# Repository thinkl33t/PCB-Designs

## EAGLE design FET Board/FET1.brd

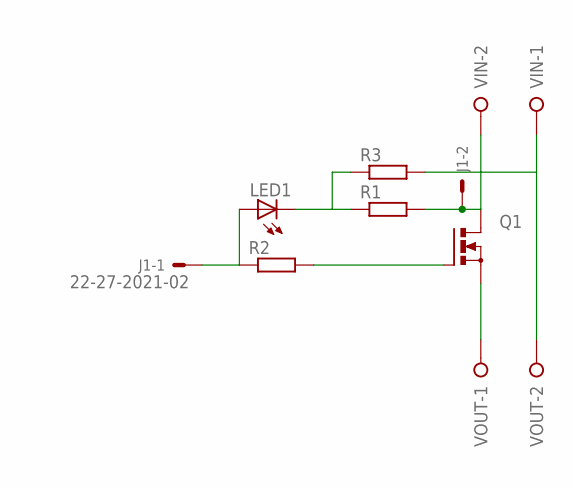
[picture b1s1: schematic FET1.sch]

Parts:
J1: 22-27-2021-02; 6410-02
LED1: LED5MM
Q1: PMOSFET_NTO220BV; TO220BV
R1, R2, R3: R-EU_0207/7; 0207/7
VIN: W237-02P; W237-132
VOUT: W237-02P; W237-132

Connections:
GIN: J1.2, Q1.D, R1.2, VIN.2
GOUT: Q1.S, VOUT.1
unnamed: Q1.G, R2.2
unnamed: LED1.K (C), R1.1, R3.1
unnamed: J1.1, LED1.A, R2.1
V+: R3.2, VIN.1, VOUT.2

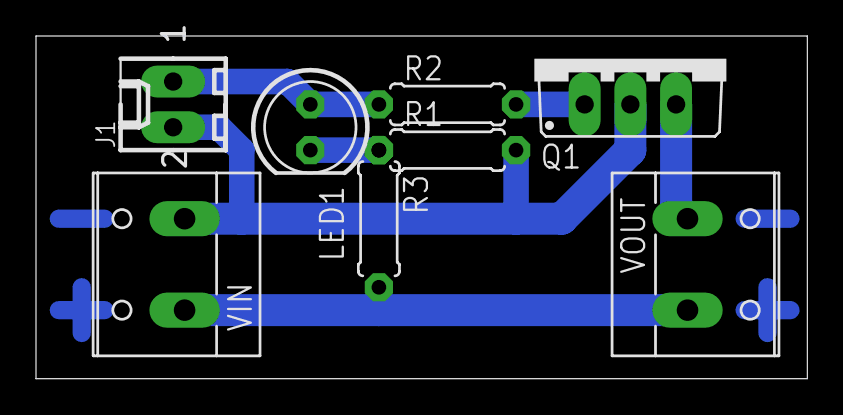
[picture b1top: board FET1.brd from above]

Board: 2 copper layers, 42.9 x 19.0 mm, 8 parts (0 on the bottom side), 6 nets.

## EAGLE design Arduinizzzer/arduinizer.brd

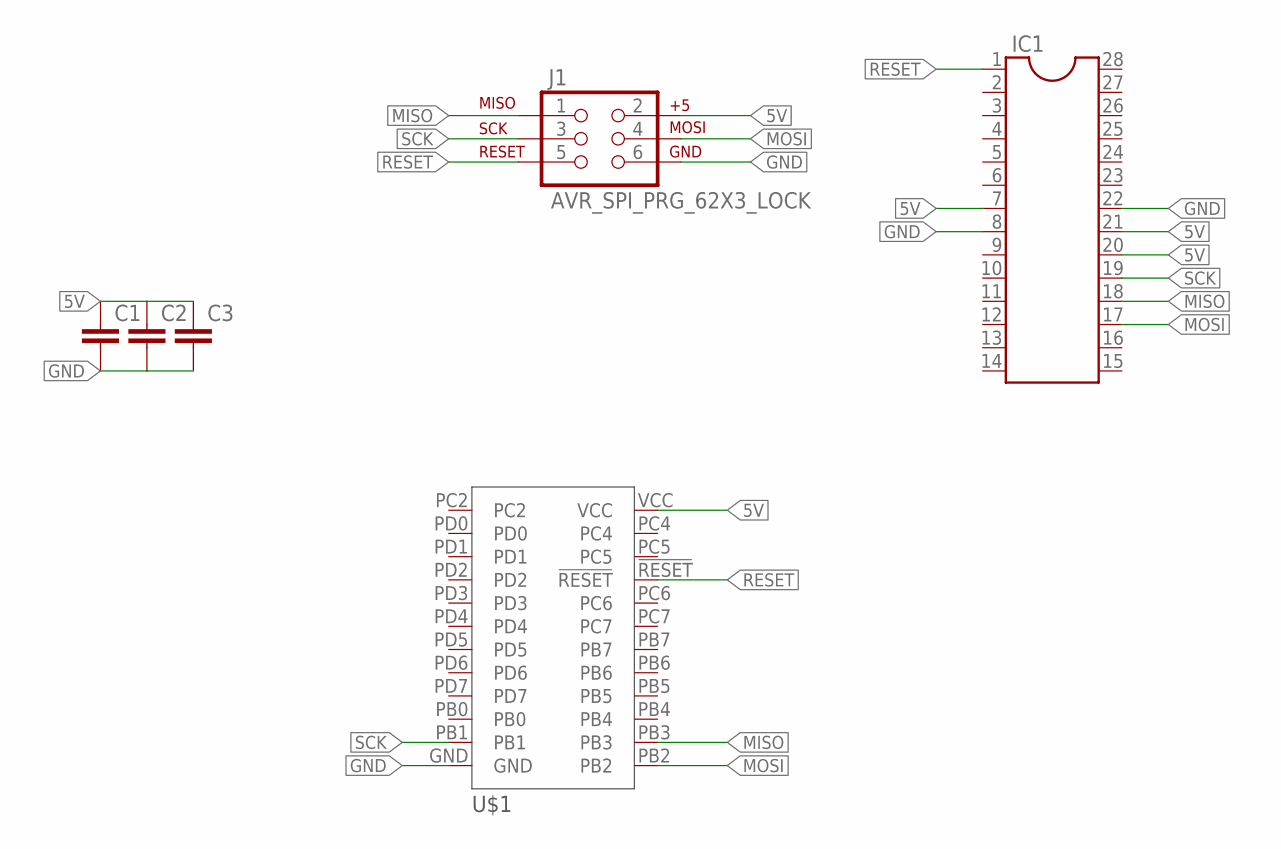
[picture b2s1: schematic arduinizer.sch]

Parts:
C1, C2, C3: C-EU025-025X050; C025-025X050
IC1: DIL28; DIL28-6
J1: AVR_SPI_PRG_62X3_LOCK; 2X3_LOCK
U$1: MINIMUSBIGPADS

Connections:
5V: C1.1, C2.1, C3.1, IC1.7, IC1.20, IC1.21, J1.2, U$1.VCC
GND: C1.2, C2.2, C3.2, IC1.8, IC1.22, J1.6, U$1.GND
MISO: IC1.18, J1.1, U$1.PB3
MOSI: IC1.17, J1.4, U$1.PB2
RESET: IC1.1, J1.5, U$1.!RESET
SCK: IC1.19, J1.3, U$1.PB1

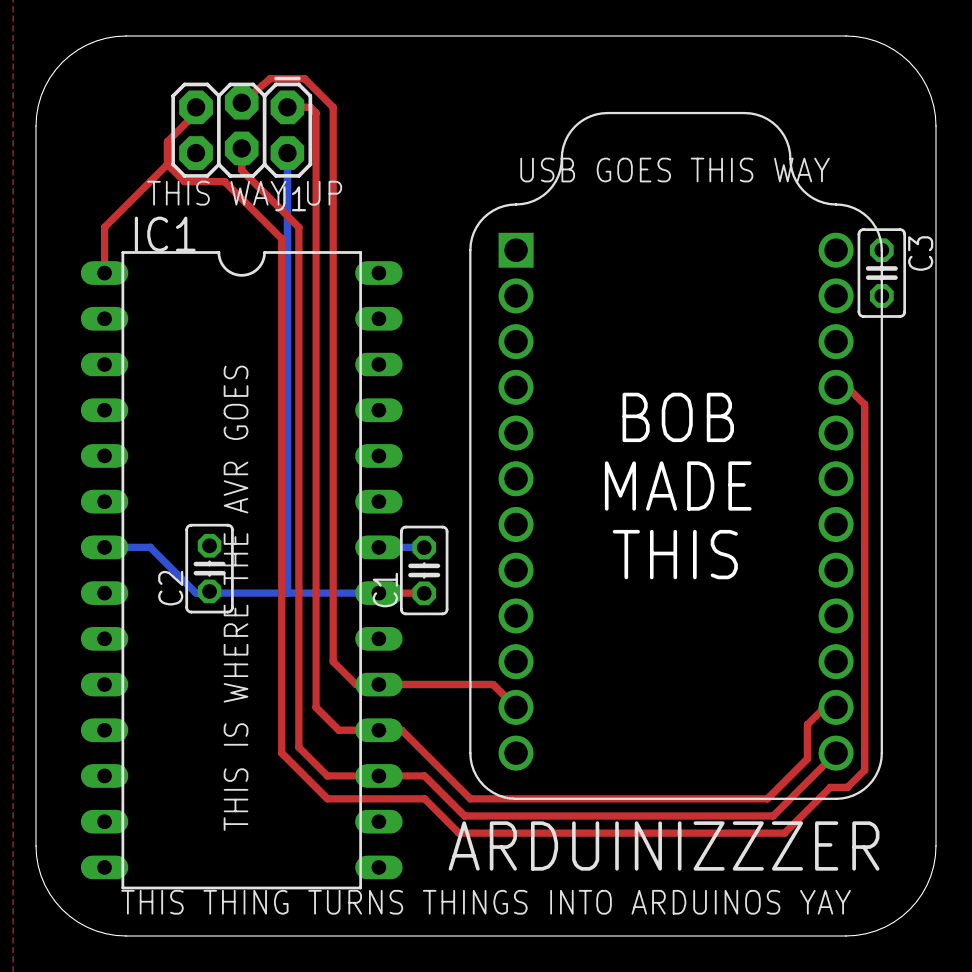
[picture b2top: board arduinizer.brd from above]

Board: 2 copper layers, 50.0 x 50.0 mm, 6 parts (0 on the bottom side), 6 nets.

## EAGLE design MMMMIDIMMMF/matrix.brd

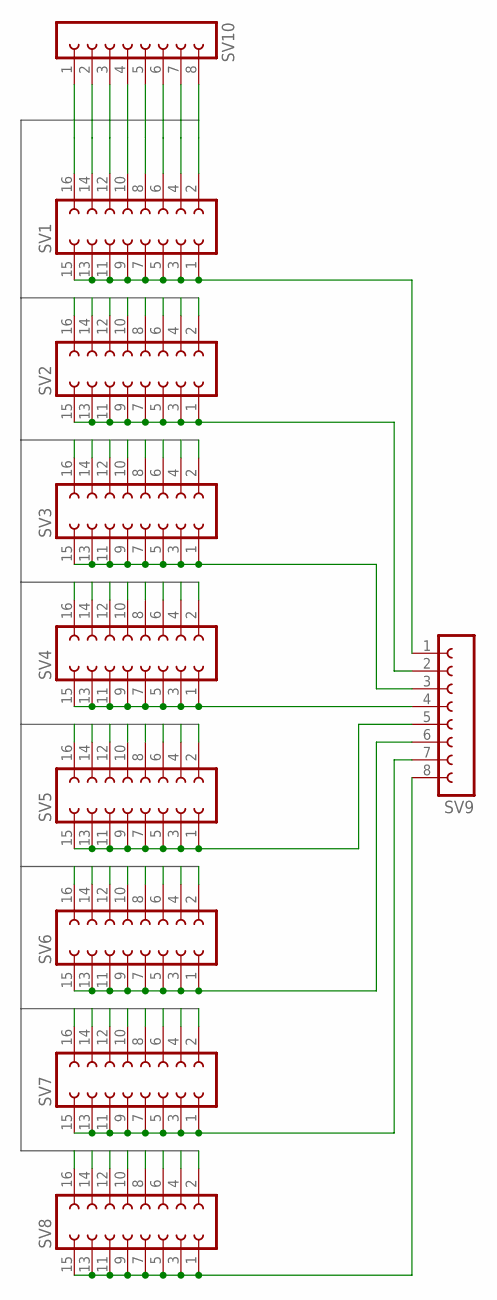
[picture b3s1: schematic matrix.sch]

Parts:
SV1, SV2, SV3, SV4, SV5, SV6, SV7, SV8: FE08-2
SV9, SV10: FE08-1; FE08

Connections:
C1: SV1.16, SV2.16, SV3.16, SV4.16, SV5.16, SV6.16, SV7.16, SV8.16, SV10.1
C2: SV1.14, SV2.14, SV3.14, SV4.14, SV5.14, SV6.14, SV7.14, SV8.14, SV10.2
C3: SV1.12, SV2.12, SV3.12, SV4.12, SV5.12, SV6.12, SV7.12, SV8.12, SV10.3
C4: SV1.10, SV2.10, SV3.10, SV4.10, SV5.10, SV6.10, SV7.10, SV8.10, SV10.4
C5: SV1.8, SV2.8, SV3.8, SV4.8, SV5.8, SV6.8, SV7.8, SV8.8, SV10.5
C6: SV1.6, SV2.6, SV3.6, SV4.6, SV5.6, SV6.6, SV7.6, SV8.6, SV10.6
C7: SV1.4, SV2.4, SV3.4, SV4.4, SV5.4, SV6.4, SV7.4, SV8.4, SV10.7
C8: SV1.2, SV2.2, SV3.2, SV4.2, SV5.2, SV6.2, SV7.2, SV8.2, SV10.8
unnamed: SV1.1, SV1.3, SV1.5, SV1.7, SV1.9, SV1.11, SV1.13, SV1.15, SV9.1
unnamed: SV2.1, SV2.3, SV2.5, SV2.7, SV2.9, SV2.11, SV2.13, SV2.15, SV9.2
unnamed: SV3.1, SV3.3, SV3.5, SV3.7, SV3.9, SV3.11, SV3.13, SV3.15, SV9.3
unnamed: SV4.1, SV4.3, SV4.5, SV4.7, SV4.9, SV4.11, SV4.13, SV4.15, SV9.4
unnamed: SV5.1, SV5.3, SV5.5, SV5.7, SV5.9, SV5.11, SV5.13, SV5.15, SV9.5
unnamed: SV6.1, SV6.3, SV6.5, SV6.7, SV6.9, SV6.11, SV6.13, SV6.15, SV9.6
unnamed: SV7.1, SV7.3, SV7.5, SV7.7, SV7.9, SV7.11, SV7.13, SV7.15, SV9.7
unnamed: SV8.1, SV8.3, SV8.5, SV8.7, SV8.9, SV8.11, SV8.13, SV8.15, SV9.8

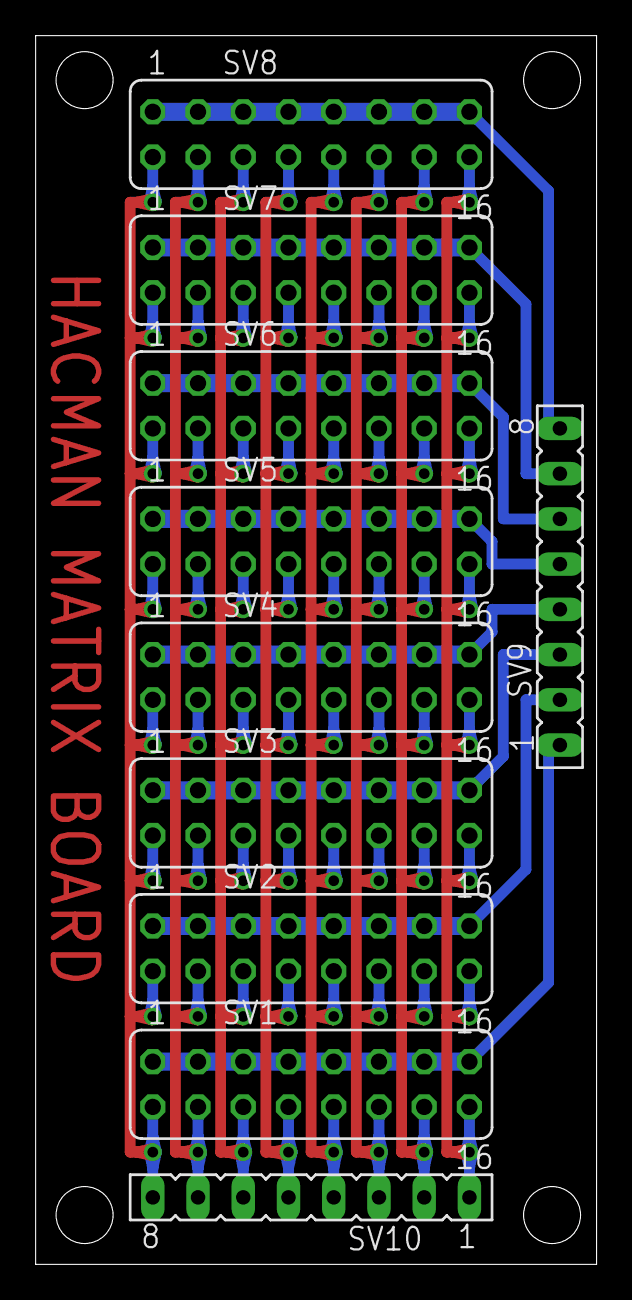
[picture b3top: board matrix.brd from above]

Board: 2 copper layers, 31.5 x 69.0 mm, 10 parts (0 on the bottom side), 16 nets.

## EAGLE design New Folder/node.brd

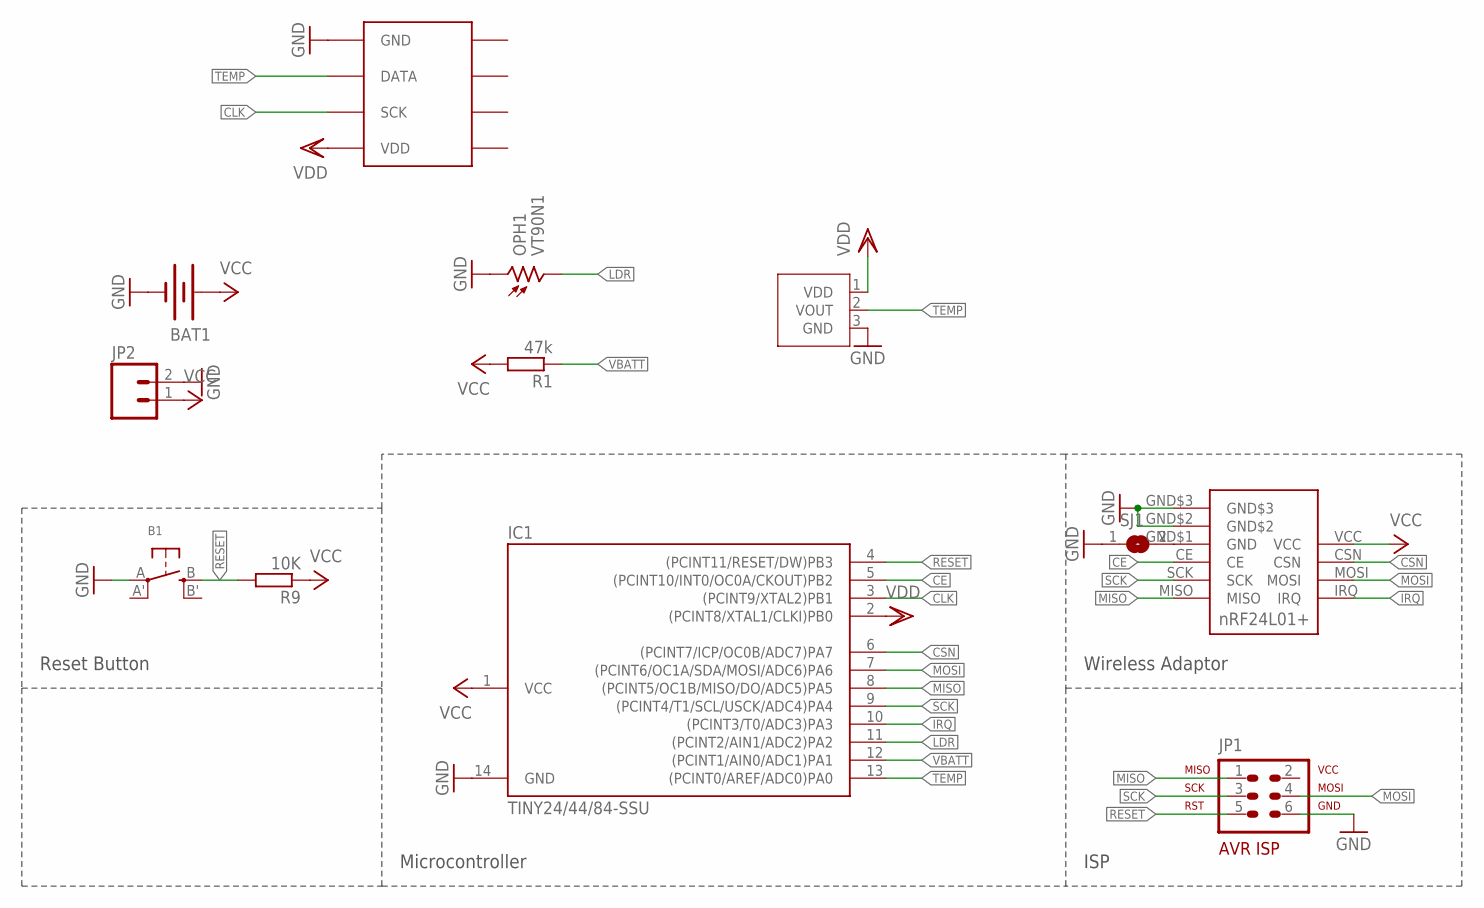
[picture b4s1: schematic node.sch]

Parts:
B1: SWITCH_TACT_SMT; EVQ-Q2
BAT1: BATTERY20SMD; BATTCON_20MM
CHINESE1: NRF24L01+CHINESE-DUAL; CHINESE-DUALPINOUT
IC1: TINY24/44/84-SSU; SOIC14
JP1: AVR-ISP-6VERT; AVR-ISP-6
JP2: M02POLAR_LOCK; MOLEX-1X2_LOCK
OPH1: VT90N1; VT900
R1: 47k; R0805
R9: 10K; R0805
SHT1: SHT11
SJ1: SJ
U$1: MCP970XTT; SOT23

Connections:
CE: CHINESE1.CE, IC1.5 ((PCINT10/INT0/OC0A/CKOUT)PB2)
CLK: IC1.3 ((PCINT9/XTAL2)PB1), SHT1.SCK
CSN: CHINESE1.CSN, IC1.6 ((PCINT7/ICP/OC0B/ADC7)PA7)
GND: B1.A, BAT1.2 (-), CHINESE1.GND$2, CHINESE1.GND$3, IC1.14 (GND), JP1.6, JP2.2, OPH1.1, SHT1.GND, SJ1.1, U$1.3 (GND)
IRQ: CHINESE1.IRQ, IC1.10 ((PCINT3/T0/ADC3)PA3)
LDR: IC1.11 ((PCINT2/AIN1/ADC2)PA2), OPH1.2
MISO: CHINESE1.MISO, IC1.8 ((PCINT5/OC1B/MISO/DO/ADC5)PA5), JP1.1
MOSI: CHINESE1.MOSI, IC1.7 ((PCINT6/OC1A/SDA/MOSI/ADC6)PA6), JP1.4
unnamed: CHINESE1.GND$1 (GND), SJ1.2
RESET: B1.B (S), IC1.4 ((PCINT11/RESET/DW)PB3), JP1.5, R9.2
SCK: CHINESE1.SCK, IC1.9 ((PCINT4/T1/SCL/USCK/ADC4)PA4), JP1.3
TEMP: IC1.13 ((PCINT0/AREF/ADC0)PA0), SHT1.DATA, U$1.2 (VOUT)
VBATT: IC1.12 ((PCINT1/AIN0/ADC1)PA1), R1.1
VCC: BAT1.1 (+), CHINESE1.VCC, IC1.1 (VCC), JP2.1, R1.2, R9.1
VDD: IC1.2 ((PCINT8/XTAL1/CLKI)PB0), SHT1.VDD, U$1.1 (VDD)

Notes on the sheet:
Wireless Adaptor
ISP
Microcontroller
Reset Button

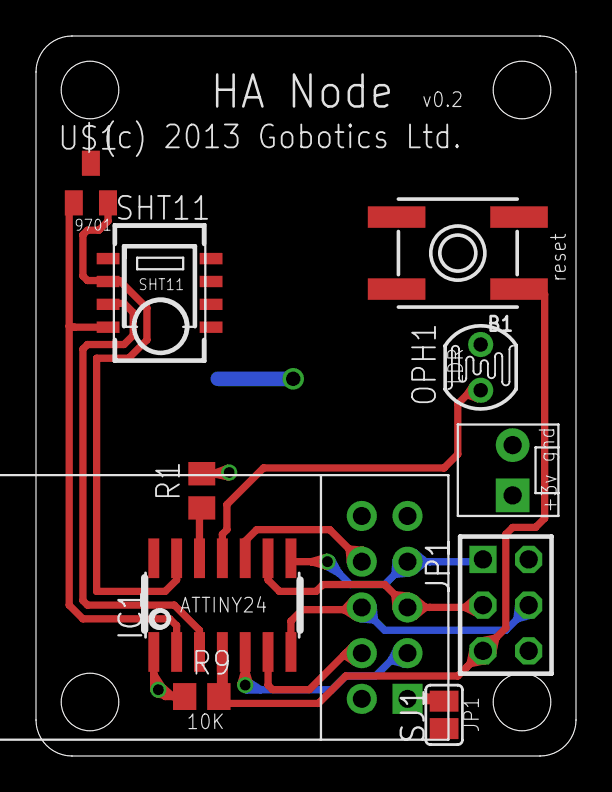
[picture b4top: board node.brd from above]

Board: 2 copper layers, 30.0 x 40.0 mm, 12 parts (1 on the bottom side), 15 nets.

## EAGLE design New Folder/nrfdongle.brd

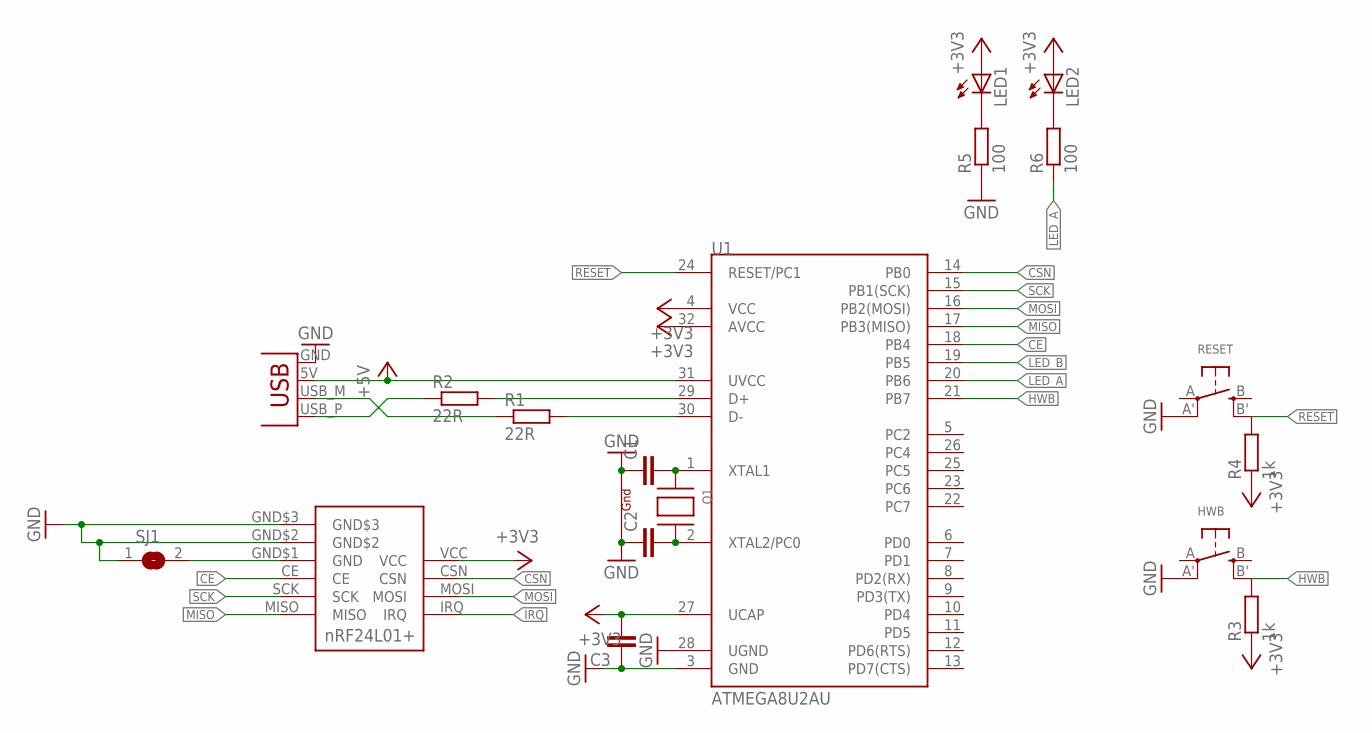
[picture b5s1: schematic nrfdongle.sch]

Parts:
C1, C2, C3: C-EUC0805; C0805
CHINESE1: NRF24L01+CHINESE-DUAL; CHINESE-DUALPINOUT
HWB: SWITCH_TACT_SMT; EVQ-Q2
LED1, LED2: LEDSML0805; SML0805
Q1: XTAL-4-3225; NX3225
R1, R2: 22R; R0805
R3, R4: 1k; R0805
R5, R6: 100; R0805
RESET: SWITCH_TACT_SMT; EVQ-Q2
SJ1: SJ
U1: ATMEGA8U2AU; TQFP32-08
X1: USBPCB; USB-A-PCB

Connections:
+3V3: C3.2, CHINESE1.VCC, LED1.A, LED2.A, R3.1, R4.1, U1.4 (VCC), U1.27 (UCAP), U1.32 (AVCC)
+5V: U1.31 (UVCC), X1.5V (VBUS)
CE: CHINESE1.CE, U1.18 (PB4)
CSN: CHINESE1.CSN, U1.14 (PB0)
GND: C1.1, C2.1, C3.1, CHINESE1.GND$2, CHINESE1.GND$3, HWB.A' (P1), Q1.2 (G1), Q1.4 (G2), R5.1, RESET.A' (P1), SJ1.1, U1.3 (GND), U1.28 (UGND), X1.GND
HWB: HWB.B' (S1), R3.2, U1.21 (PB7)
IRQ: CHINESE1.IRQ
LED_A: R6.1, U1.20 (PB6)
LED_B: U1.19 (PB5)
MISO: CHINESE1.MISO, U1.17 (PB3(MISO))
MOSI: CHINESE1.MOSI, U1.16 (PB2(MOSI))
unnamed: R1.1, X1.USB_M (D-)
unnamed: R2.1, X1.USB_P (D+)
unnamed: R1.2, U1.30 (D-)
unnamed: R2.2, U1.29 (D+)
unnamed: CHINESE1.GND$1 (GND), SJ1.2
unnamed: C1.2, Q1.1 (X1), U1.1 (XTAL1)
unnamed: C2.2, Q1.3 (X2), U1.2 (XTAL2/PC0)
unnamed: LED1.C, R5.2
unnamed: LED2.C, R6.2
RESET: R4.2, RESET.B' (S1), U1.24 (RESET/PC1)
SCK: CHINESE1.SCK, U1.15 (PB1(SCK))

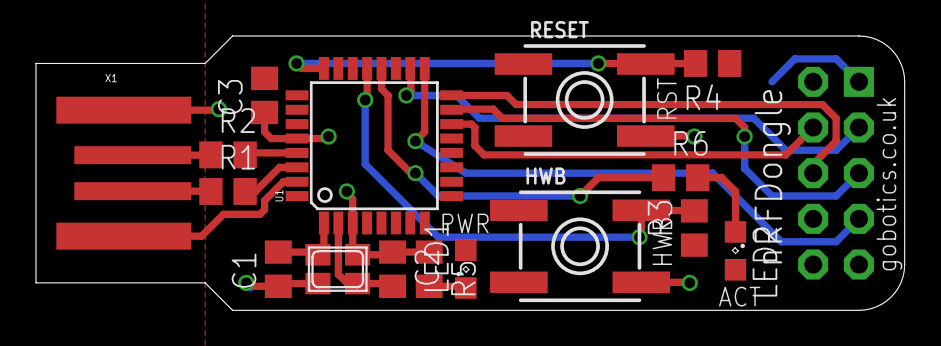
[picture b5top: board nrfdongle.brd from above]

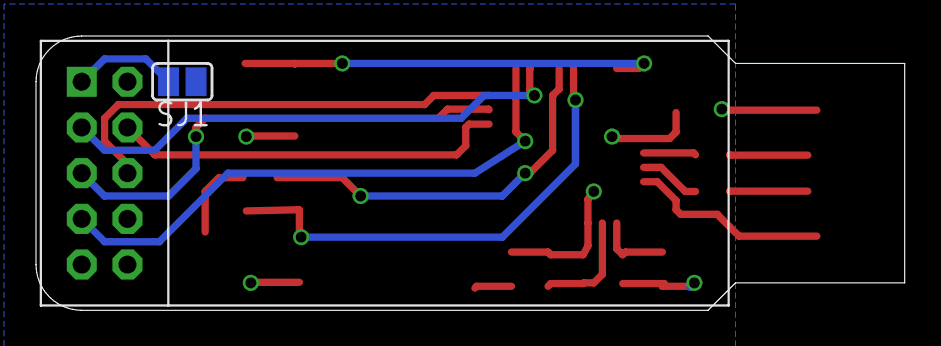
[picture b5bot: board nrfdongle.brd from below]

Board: 2 copper layers, 48.3 x 15.2 mm, 18 parts (2 on the bottom side), 20 nets.

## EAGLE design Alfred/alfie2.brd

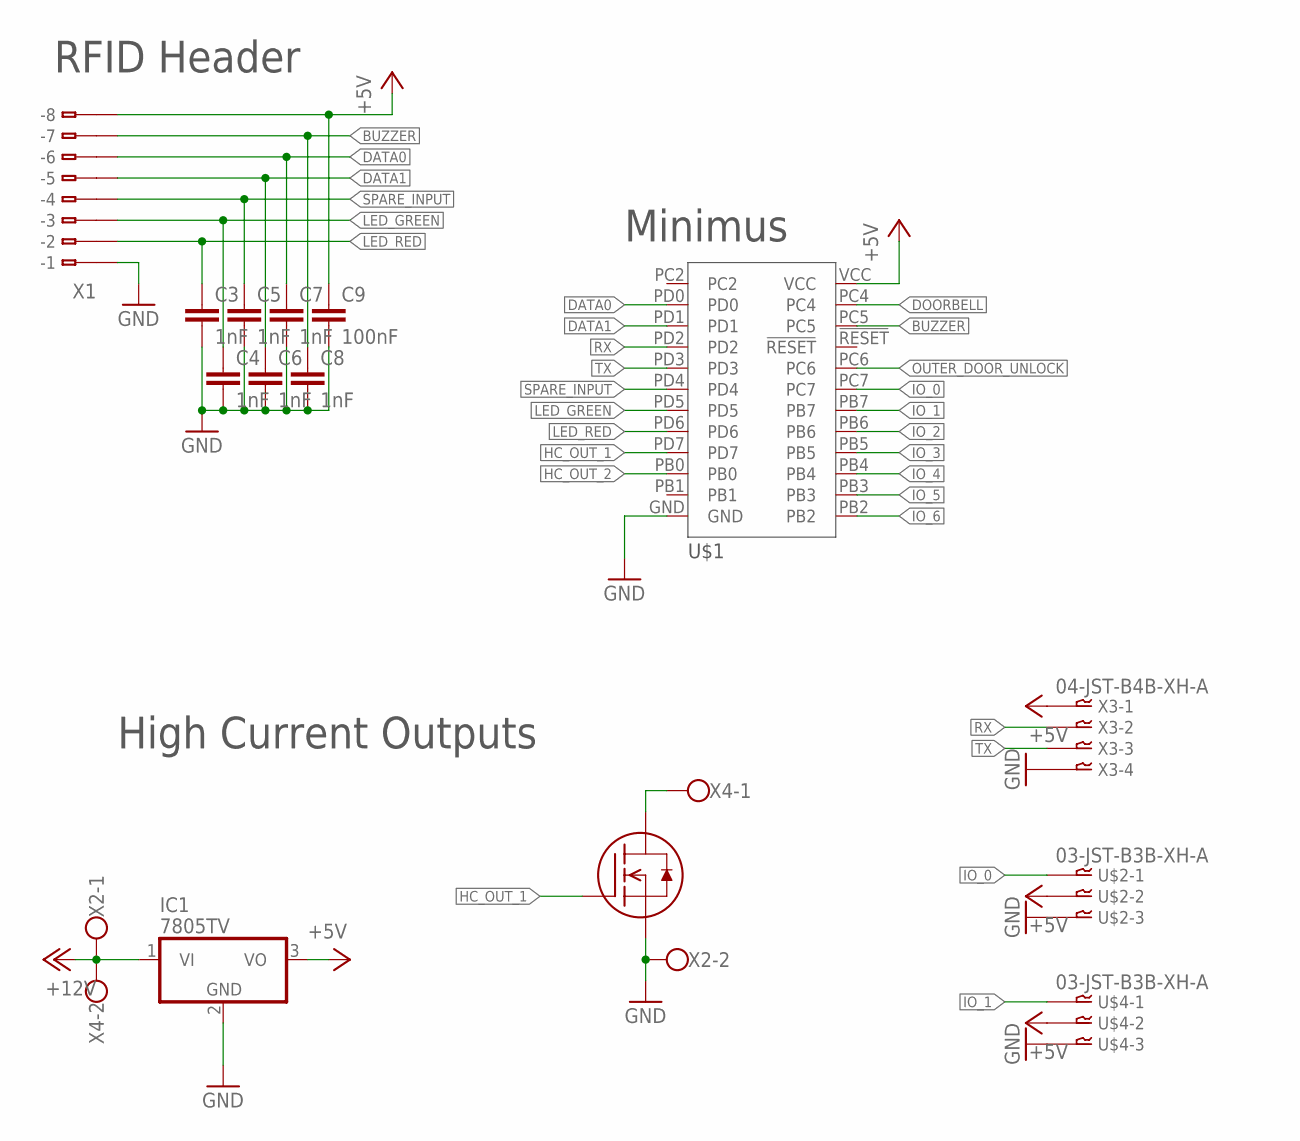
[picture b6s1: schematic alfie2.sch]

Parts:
C3, C4, C5, C6, C7, C8: 1nF; C0805
C9: 100nF; C0805
IC1: 7805TV; TO220V
U$1: MINIMUS
U$2, U$4: 03-JST-B3B-XH-A; B3B-XH
U$3: NTF3055L108T1GTAB; SOT223
X1: 233-508
X2, X4: W237-102
X3: 04-JST-B4B-XH-A; B4B-XH

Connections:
+5V: C9.1, IC1.3 (VO), U$1.VCC, U$2.P$2, U$4.P$2, X1.B8 (B-8), X3.P$1
+12V: IC1.1 (VI), X2.1, X4.2
BUZZER: C8.1, U$1.PC5, X1.B7 (B-7)
DATA0: C7.1, U$1.PD0, X1.B6 (B-6)
DATA1: C6.1, U$1.PD1, X1.B5 (B-5)
DOORBELL: U$1.PC4
GND: C3.2, C4.2, C5.2, C6.2, C7.2, C8.2, C9.2, IC1.2 (GND), U$1.GND, U$2.P$3, U$3.3 (S), U$4.P$3, X1.B1 (B-1), X2.2, X3.P$4
HC_OUT_1: U$1.PD7, U$3.1 (G)
HC_OUT_2: U$1.PB0
IO_0: U$1.PC7, U$2.P$1
IO_1: U$1.PB7, U$4.P$1
IO_2: U$1.PB6
IO_3: U$1.PB5
IO_4: U$1.PB4
IO_5: U$1.PB3
IO_6: U$1.PB2
LED_GREEN: C4.1, U$1.PD5, X1.B3 (B-3)
LED_RED: C3.1, U$1.PD6, X1.B2 (B-2)
unnamed: U$3.4 (D), X4.1
OUTER_DOOR_UNLOCK: U$1.PC6
RX: U$1.PD2, X3.P$2
SPARE_INPUT: C5.1, U$1.PD4, X1.B4 (B-4)
TX: U$1.PD3, X3.P$3

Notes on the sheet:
High Current Outputs
Minimus
RFID Header

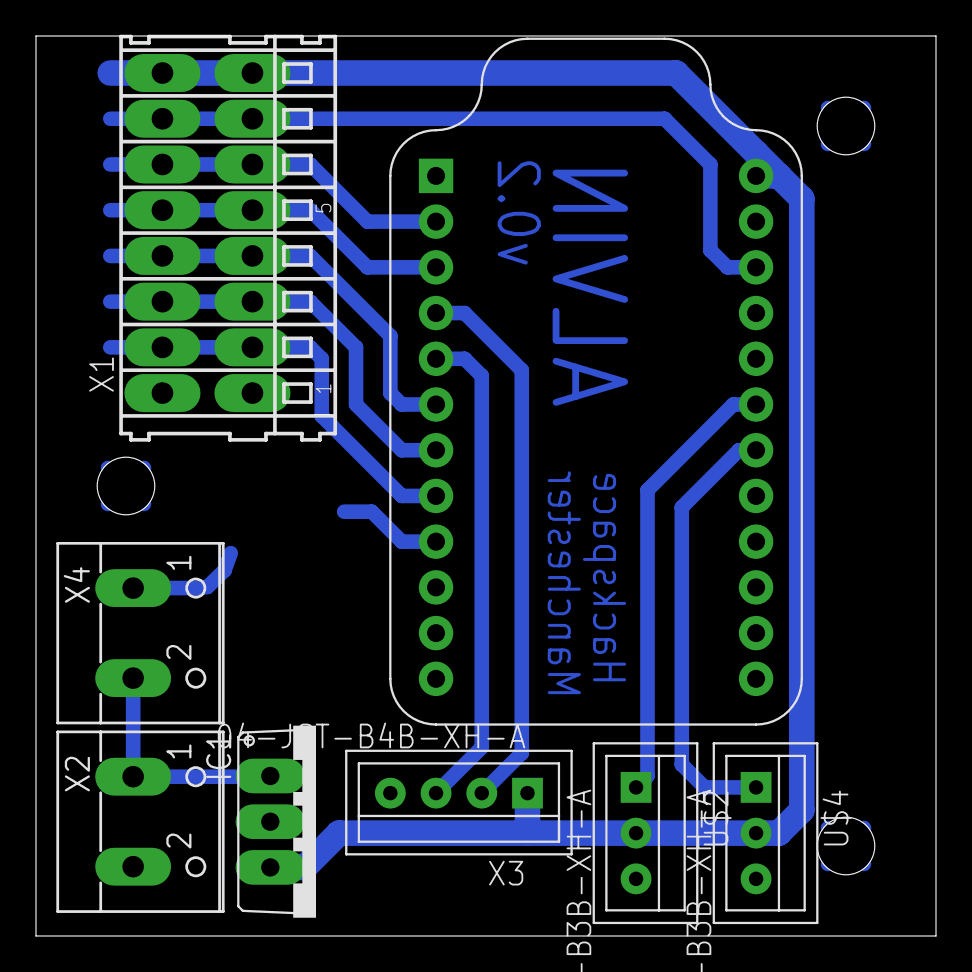
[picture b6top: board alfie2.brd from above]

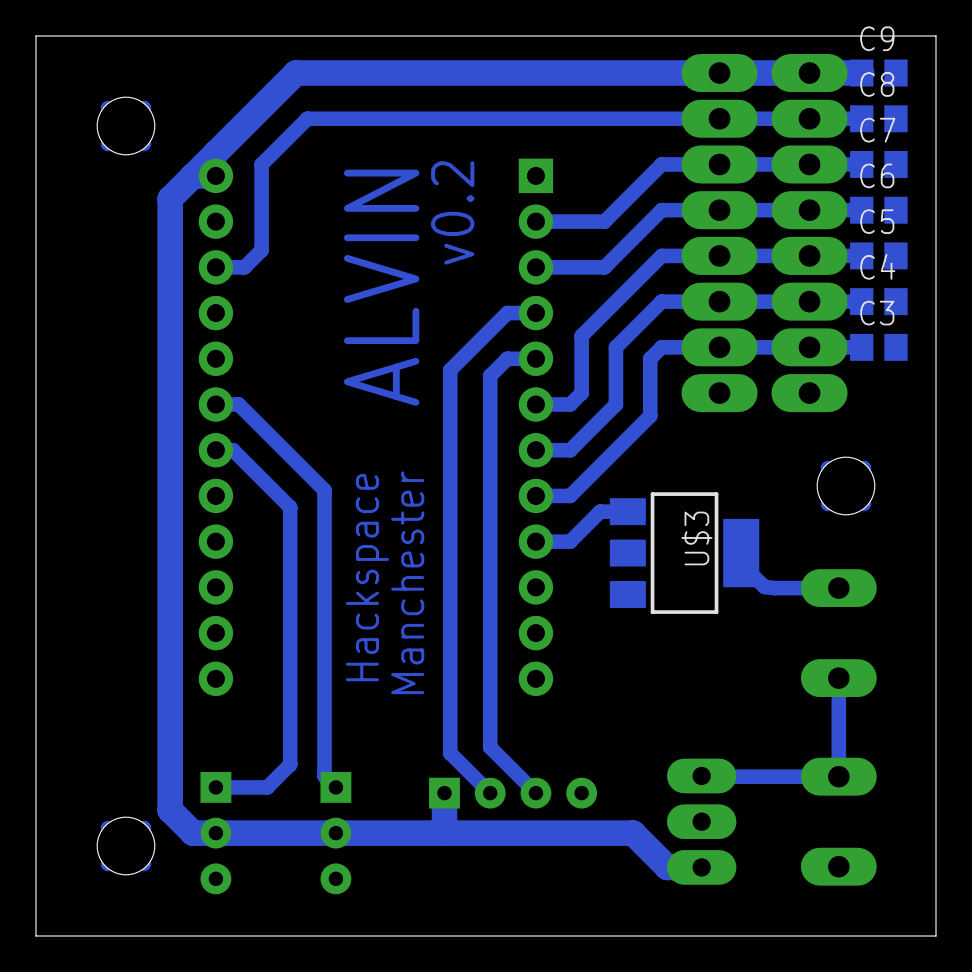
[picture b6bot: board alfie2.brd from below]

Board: 2 copper layers, 50.0 x 50.0 mm, 16 parts (8 on the bottom side), 15 nets.

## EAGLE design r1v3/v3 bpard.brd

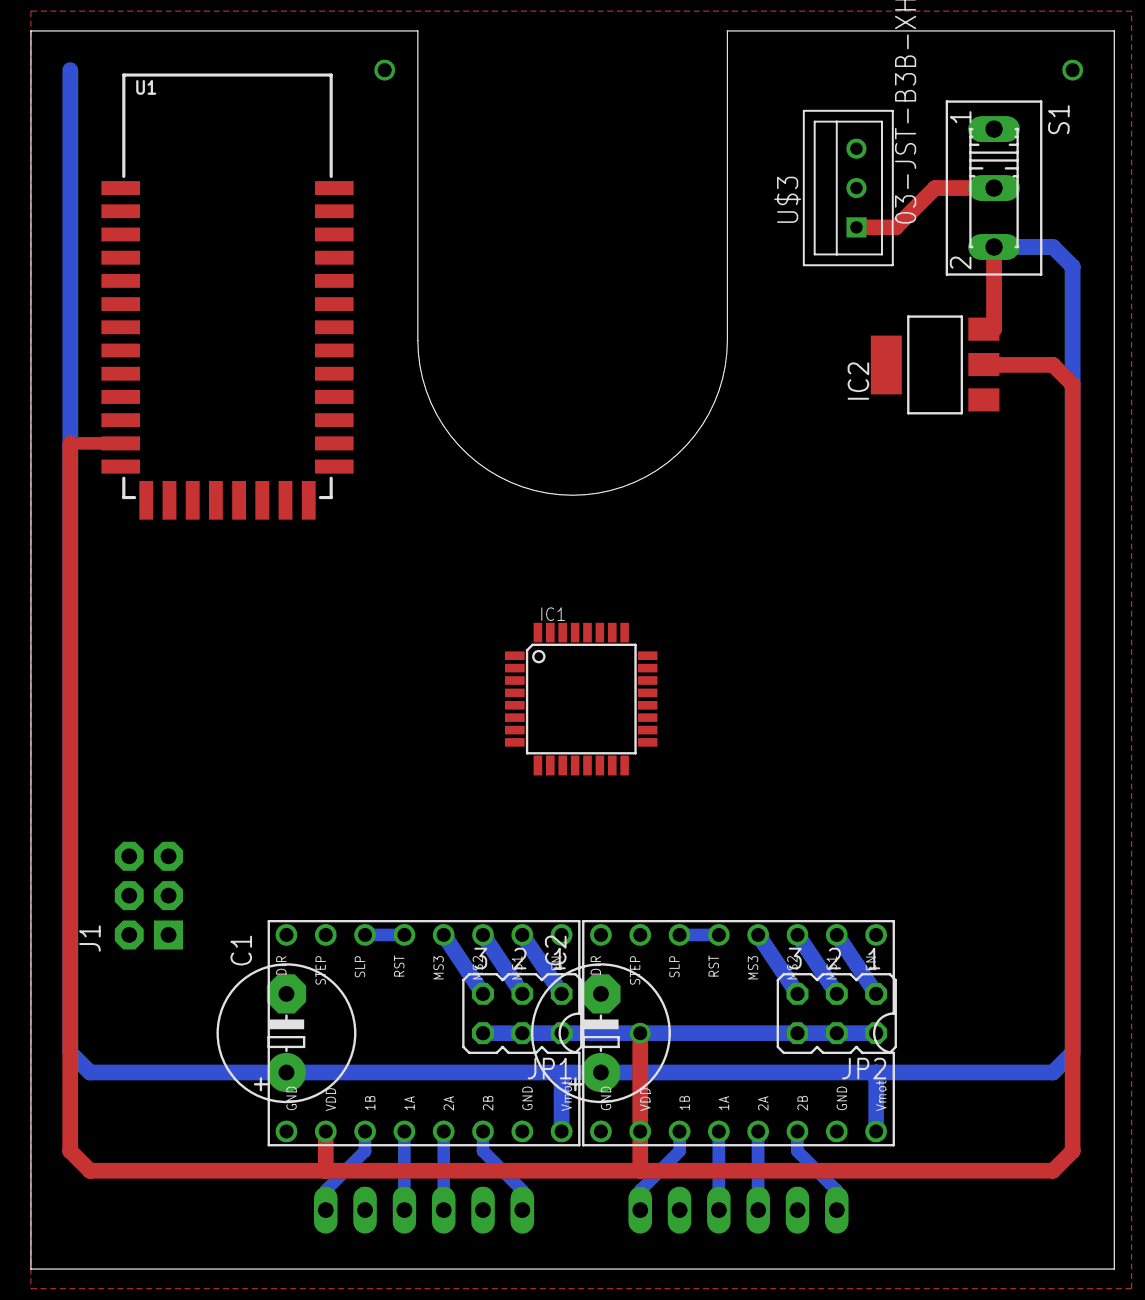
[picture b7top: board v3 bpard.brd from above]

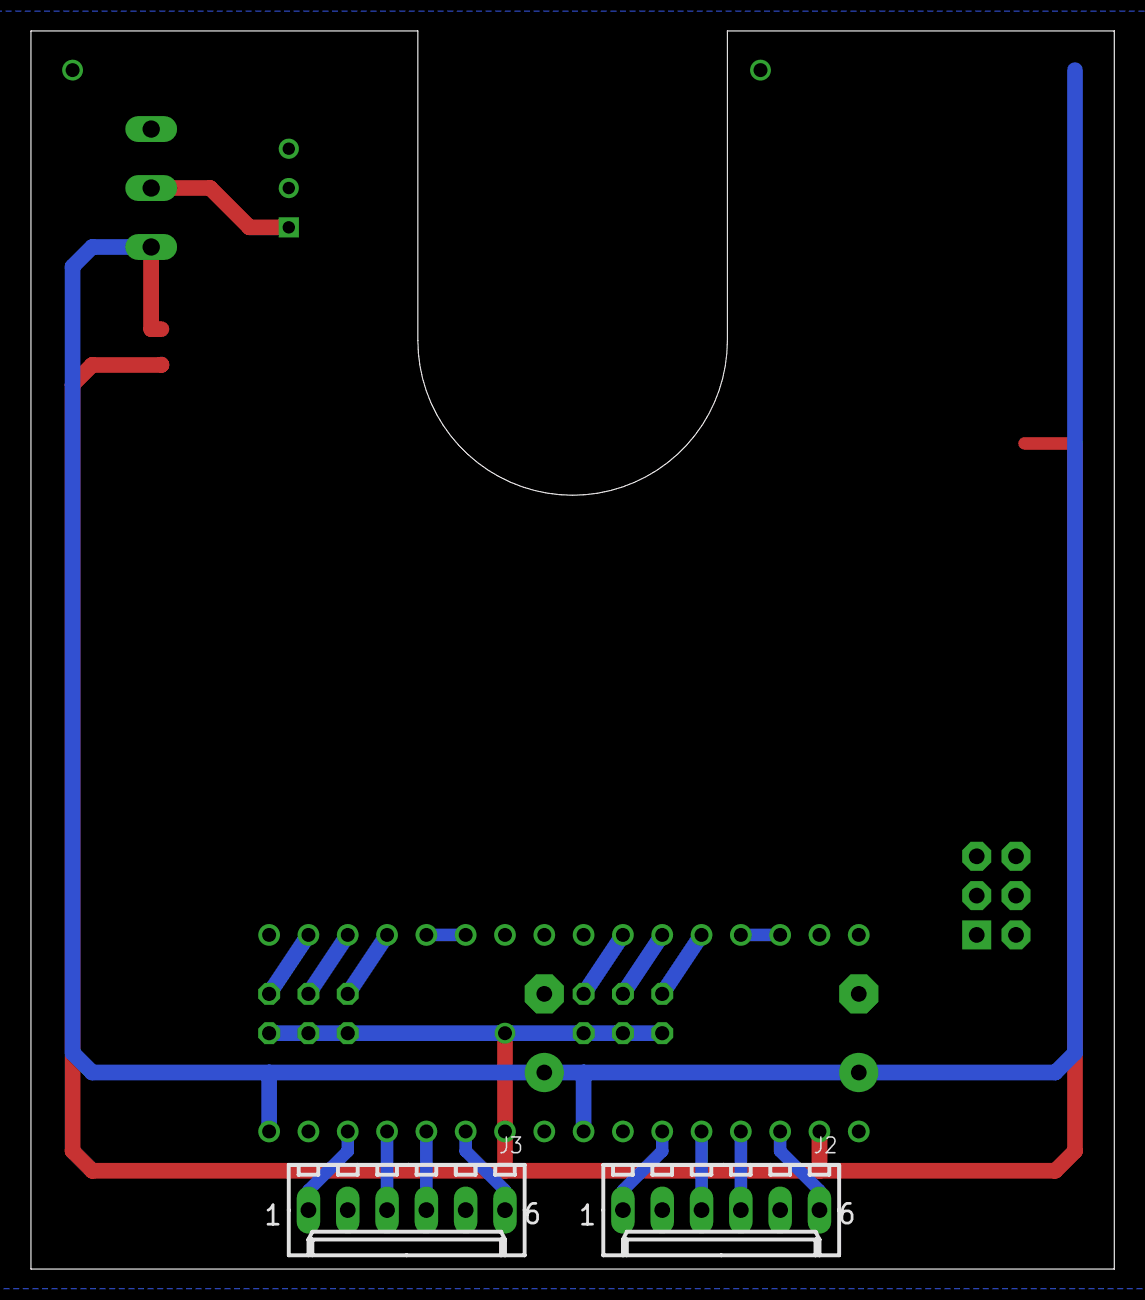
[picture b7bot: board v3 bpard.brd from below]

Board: 2 copper layers, 70.0 x 80.0 mm, 14 parts (2 on the bottom side), 20 nets.

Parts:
C1, C2: E5-8,5
IC1: ATMEGA168-AU; TQFP32-08
IC2: REG1117; SOT223
J1: AVR_SPI_PRG_6NS; 2X3-NS
J2, J3: 22-27-2061-06; 6410-06
JP1, JP2: JP3Q
S1: 255SB
U1: BLUETOOTH_MODULE
U$1, U$2: POLOLU_A4983CARRIER; A4988BREAKOUT
U$3: 03-JST-B3B-XH-A; B3B-XH

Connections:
+3V3: IC1.4, IC1.6, IC1.18, IC2.2, JP1.2, JP1.4, JP1.6, JP2.2, JP2.4, JP2.6, U1.12, U$1.VDD, U$2.VDD
GND: C1.-, C2.-, IC1.3, IC1.5, IC1.21, IC2.1, J1.6, U1.13, U1.14, U1.21, U1.22, U$1.GND, U$1.GND@0, U$2.GND, U$2.GND@0, U$3.P$3
unnamed: J3.1, U$2.2B
unnamed: J3.3, U$2.2A
unnamed: J3.4, U$2.1A
unnamed: J3.6, U$2.1B
unnamed: J2.1, U$1.2B
unnamed: J2.3, U$1.2A
unnamed: J2.4, U$1.1A
unnamed: J2.6, U$1.1B
unnamed: JP2.5, U$2.MS3
unnamed: JP1.3, U$1.MS2
unnamed: JP2.1, U$2.MS1
unnamed: JP1.1, U$1.MS1
unnamed: JP2.3, U$2.MS2
unnamed: JP1.5, U$1.MS3
unnamed: S1.2, U$3.P$1
unnamed: U$1.RST, U$1.SLP
unnamed: U$2.RST, U$2.SLP
V+: C1.+, C2.+, IC2.3, S1.3, U$1.VMOT, U$2.VMOT

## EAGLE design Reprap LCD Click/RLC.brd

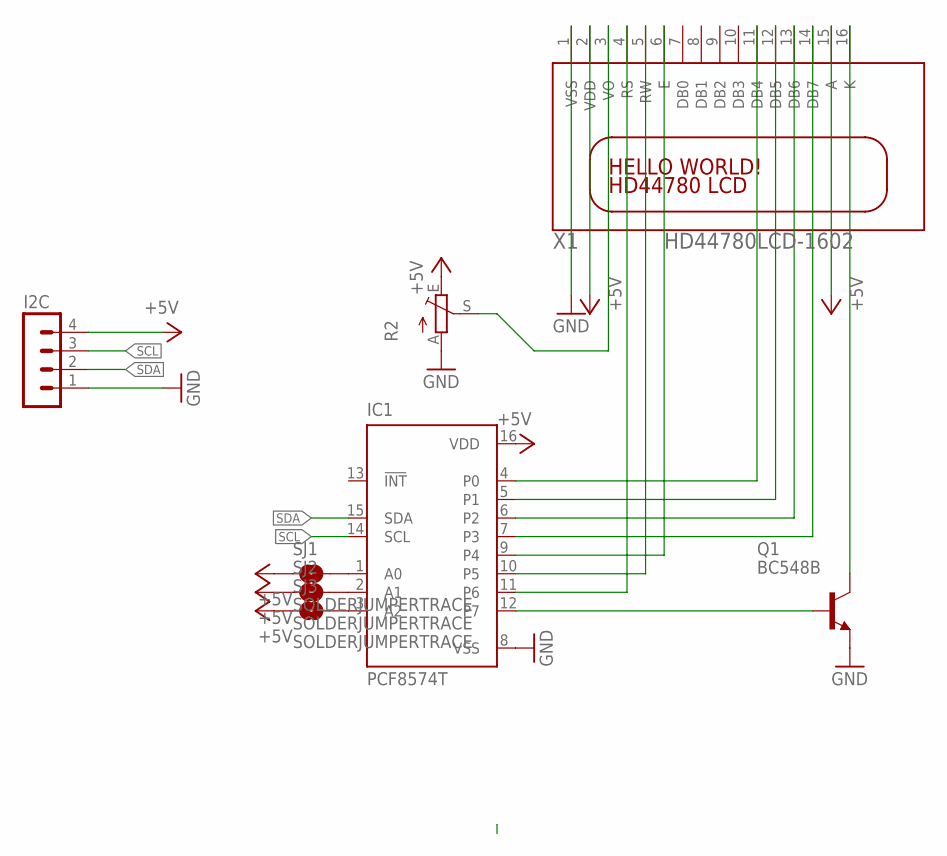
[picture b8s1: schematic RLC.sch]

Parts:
I2C: MA04-1
IC1: PCF8574T; SO16W
Q1: BC548B; TO92-EBC
R2: TRIM_EU-CA6V; CA6V
SJ1, SJ2, SJ3: SOLDERJUMPERTRACE; SJ_2S-TRACE
X1: HD44780LCD-1602; LCD1602

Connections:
+5V: I2C.4, IC1.16 (VDD), R2.E, SJ1.1, SJ2.1, SJ3.1, X1.2 (VDD), X1.15 (A)
GND: I2C.1, IC1.8 (VSS), Q1.E, R2.A, X1.1 (VSS)
unnamed: IC1.1 (A0), SJ1.2
unnamed: IC1.2 (A1), SJ2.2
unnamed: IC1.3 (A2), SJ3.2
unnamed: IC1.4 (P0), X1.11 (DB4)
unnamed: IC1.5 (P1), X1.12 (DB5)
unnamed: IC1.6 (P2), X1.13 (DB6)
unnamed: IC1.7 (P3), X1.14 (DB7)
unnamed: IC1.9 (P4), X1.6 (E)
unnamed: IC1.10 (P5), X1.5 (RW)
unnamed: IC1.11 (P6), X1.4 (RS)
unnamed: IC1.12 (P7), Q1.B
unnamed: Q1.C, X1.16 (K)
unnamed: R2.S, X1.3 (VO)
SCL: I2C.3, IC1.14 (SCL)
SDA: I2C.2, IC1.15 (SDA)

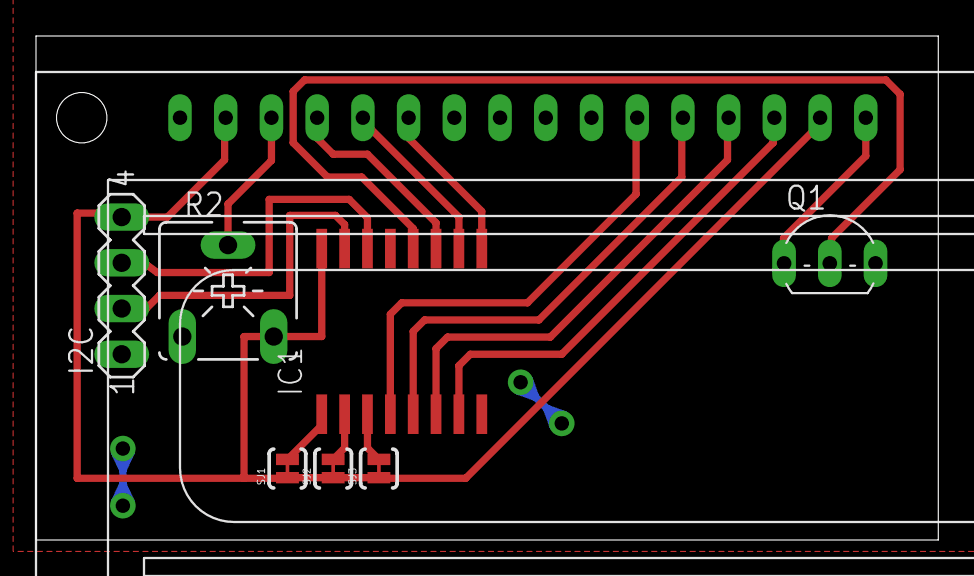
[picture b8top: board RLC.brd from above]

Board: 2 copper layers, 50.1 x 28.0 mm, 8 parts (0 on the bottom side), 17 nets.

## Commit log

2011-09-15 Eagle files for some of my PCB designs
2011-09-16 Added other libraries
2011-09-16 Added Project a sketch v2 board and xbee usb adaptor
2011-09-16 added gitignore to ignore eagle temp files
2011-09-16 Added mini stylophone, new version of magnetic encoder, updated as5035 file
2011-09-16 removed prototype stylophone, added real one
2011-09-16 added R2v1 LED board and XBee RC rx
2011-09-16 added nbitwonder library and updated gitignore to ignore osx tempfiles
2011-09-23 Magnetic Encoder v2.0a
2011-09-28 new version of MCE with fixed library
2011-09-28 finished new version of MQE
2011-09-29 added darlington motor driver
2011-09-29 Tiny Tweaks
2011-09-30 Added Grebers and images, plus tweaked DMD to look pretty
2011-09-30 Release version of as5035
2011-10-10 Added latest version of MQE, First versions of line follower and Linq
2011-10-10 Added line follower new version + couple of libraries.
2011-10-10 Latest version of line follower. needs FETs changing out to FDN302P or FDN335N
2011-10-12 Added line follower new version.
2012-02-12 Keyboard encoder addon for Minimus
2012-03-23 added LAOS adaptor, and first version of pod PCBs.
2012-03-23 pods v2, removed groundplane due to device being home-etched
2012-03-23 pods v3, changed ot using MOSFET tab instead of pins to simplify routing
2012-03-23 pods v4, added mounting holes
2012-03-23 pods v5, prettied up schematic and moved some tracks
2012-03-23 pods v6, added capacitor and hacman logo
2012-04-03 Pods v7, moved a line, exported a pdf for printing
2012-04-05 added mainboard v1, pods v8
2012-04-10 pods v7
2012-04-11 Mainboard v0.2 - added PWM chips
2012-04-16 R3 motor test board for breadboarding
2012-04-16 test rj45 board
2012-04-16 moved header on rj45 board
2012-04-16 added printed things to breakout boards
2012-05-01 new library for r3 parts
2012-05-01 Loads of eagle stuff
2012-05-01 first version of drive board and motor library
2012-05-01 started work on r3 drive PCB
2012-05-02 proto board, moved other things around
2012-05-02 updated Prototype
2012-05-11 Added operation shield
2012-05-28 r3 protoboard release version, merged home automation node v0.1
2012-06-15 change some libraries, add home automation node v1
2012-06-15 Wireless button PCB
2012-06-22 Wireless Button thingy
2012-09-26 Minimus ADC shield
2012-09-27 First version of Alfie board
2012-09-27 Added diodes and resistors.
2012-09-28 Added expansion header, re routed the FETs a little
2012-09-28 Added decoupling, tidied up schematic
2012-09-28 Added bigass cap for relays
2012-09-28 Tweaked restring settings
2012-10-17 added pdf of alfie schematic
2012-11-15 Applied bjdooks patches to bring this to the board as etched.
2013-01-28 added SD level shifter, first version of reprap click encoder, and some libraries
2013-01-28 panelized level shifter, ran gerber export
2013-02-15 v0.1 of SiNE
2013-02-15 added v0.1 gerbers and new images
2013-04-02 r1v3, reprap LCD clicker, alvin board
2013-04-02 alfie2 v0.2
2013-04-02 alfie2 v0.2 - visicut laser cutter file
2013-04-02 Flipped direction of PLF for lasering
2013-04-04 Added nrf dongle v0.1
2013-04-10 Added HA node v0.1, and libraries for it
2013-04-10 Added HA node v0.2, now with battery voltage monitoring
2013-04-10 Removed teardrops script
2013-07-17 MMMMIDIMMMF matrix PCB
2013-07-18 Matrix board
2013-08-21 Added arduinizzer
2013-08-21 Added arduinizzer PCB files
2013-11-14 FET board 1.0, home pcb design rules

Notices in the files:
New Folder/node.brd:
(c) 2013 Gobotics Ltd.
parts and their libraries:
microbuilder: This work is placed in the public domain, and may be freely used for commercial and non-commercial work with the following conditions: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
SparkFun: Licensing: CC v3.0 Share-Alike You are welcome to use this library for commercial purposes.
